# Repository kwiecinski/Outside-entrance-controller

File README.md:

# Outside-entrance-controller
Controller check if someone has entered through the gate/wicket (using photocell) or rang the bell switch. Then sends information by radio module to the receiver that gives a sound signal.

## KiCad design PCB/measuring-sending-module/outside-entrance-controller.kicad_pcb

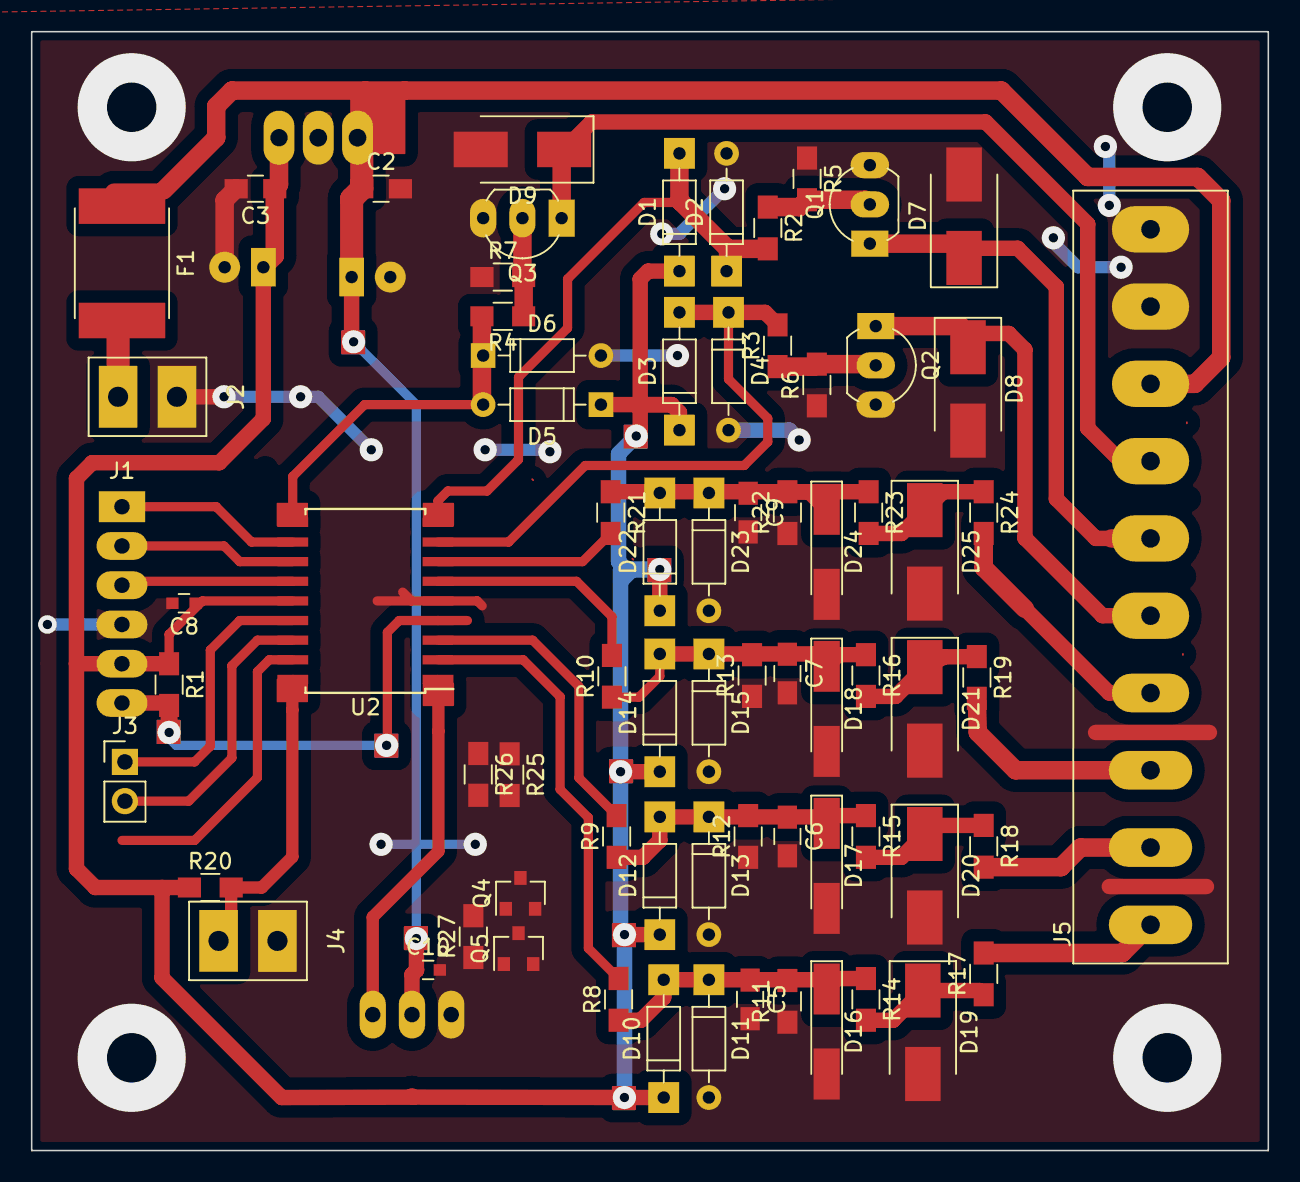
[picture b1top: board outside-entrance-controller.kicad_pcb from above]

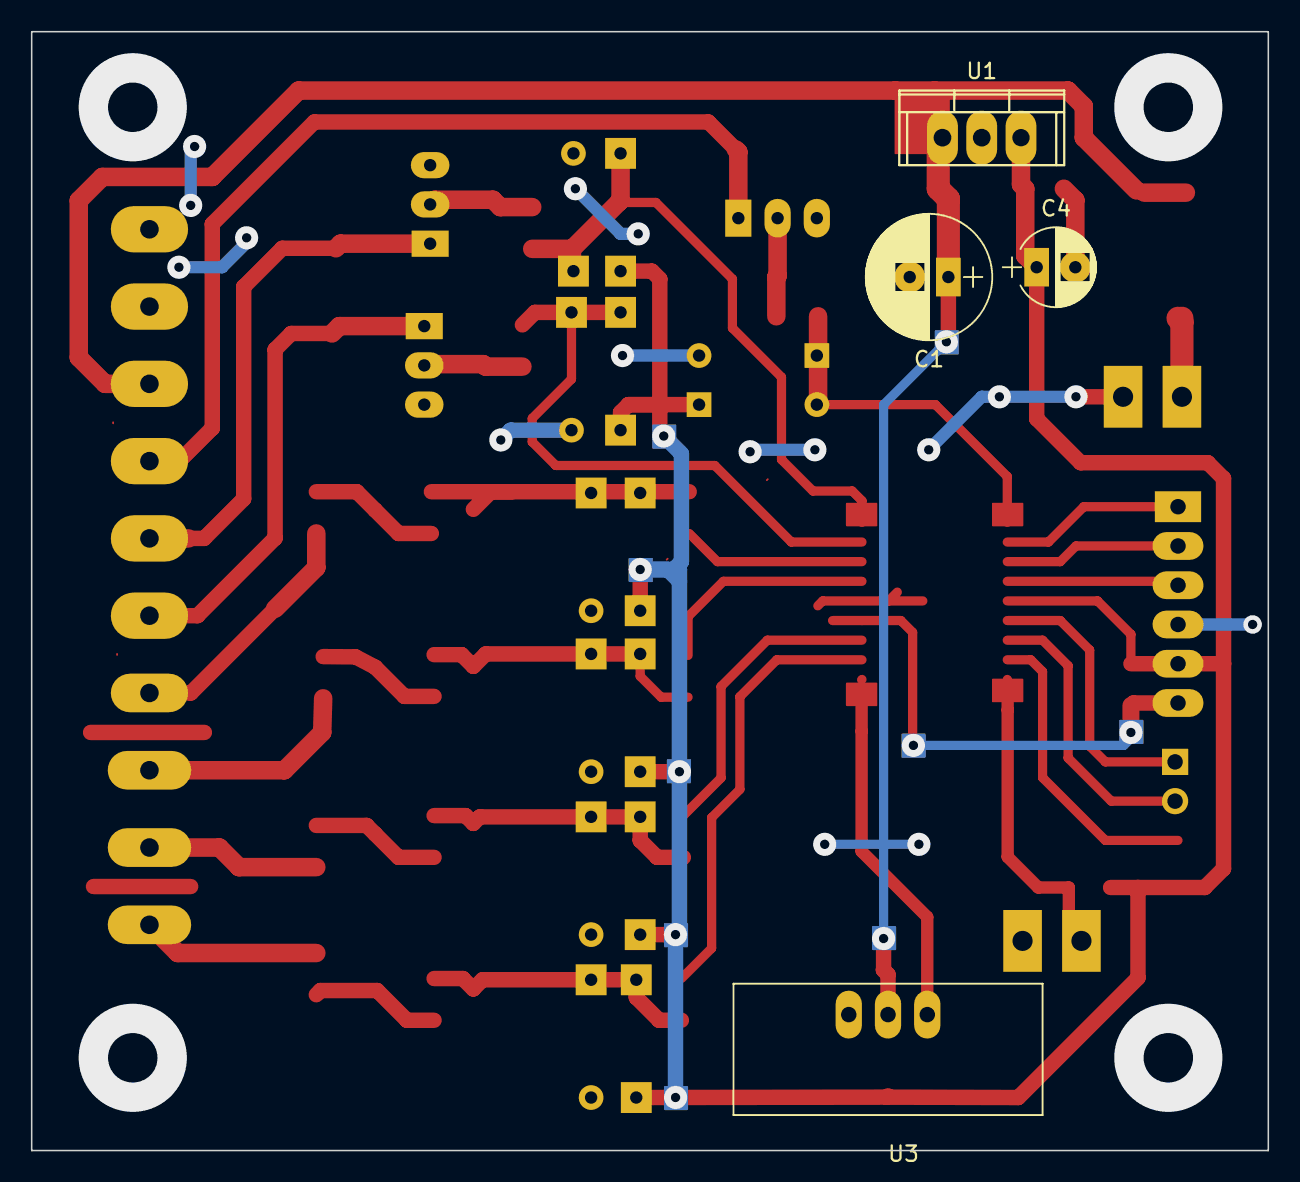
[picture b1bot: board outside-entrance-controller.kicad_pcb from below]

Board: 2 copper layers, 80.0 x 72.4 mm, 76 parts (4 on the bottom side), 42 nets.

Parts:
C1: 470u; CP_Radial_D8.0mm_P2.50mm
C2, C3: 100n; C_0805_HandSoldering
C4: 100u; CP_Radial_D5.0mm_P2.50mm
C5, C6, C7, C9: C; C_0805_HandSoldering
C8, C10: 100n; C_0603
D1, D2, D3, D4, D5, D6, D10, D11, D12, D13, D14, D15, D22, D23: 1N4148; D_DO-35_SOD27_P7.62mm_Horizontal
D7: x; D_SMB_Handsoldering
D8, D9, D19, D20, D21, D25: D_TVS; D_SMB_Handsoldering
D16, D17, D18, D24: 4V7; D_MiniMELF_Handsoldering
F1: 1,5A; Fuse_SMD2920
J1: ICP; Pin_Header_Straight_1x06_Pitch2.54mm
J2: Power-Supply-12V; Conn_1x2_wire
J3: Conn_01x02; Pin_Header_Straight_1x02_Pitch2.54mm
J4: Gate-SW; Conn_1x2_wire
J5: Screw_Terminal_01x10; Screw-Terminal-5.00mm-10pin
Q1, Q2, Q3: BC547; TO-92_Inline_Wide
Q4: BC807; SOT-23
Q5: BC817; SOT-23
R1, R5, R6, R7, R20, R26, R27: 10k; R_0805_HandSoldering
R2, R3, R4: 2k2; R_0805_HandSoldering
R8, R9, R10, R21: 1M; R_0805_HandSoldering
R11, R12, R13, R22: 100k; R_0805_HandSoldering
R14, R15, R16, R23: 1k; R_0805_HandSoldering
R17, R18, R19, R24: 10R; R_0805_HandSoldering
R25: 4k7; R_0805_HandSoldering
U1: L7805; TO-220
U2: PIC16F819-ISO; SOIC-18W_7.5x11.6mm_Pitch1.27mm
U3: 433MHz-Transmitter; 433MHz-Trasmitter

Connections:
+5V: C3.1, C4.1, C8.1, D1.1, D3.1, D5.1, D10.1, D12.1, D14.1, D22.1, J1.5, R1.1, R20.1, U1.3, U2.14
+12V: C1.1, C2.1, C10.1, F1.1, J5.8, Q4.2, R26.2, U1.1
/PGC: J1.2, U2.12
/PGD: J1.3, U2.13
/RA6: J3.1, U2.15
/RA7: J3.2, U2.16
/RST: J1.6, R1.2, U2.4
/TX: J1.1, U2.11
/bell_wicket: J5.3, R19.2
/bell_wicket_uc: R10.2, U2.6
/gate_sw: J4.2, R20.2, U2.18
/input_1: J5.4, R24.2
/input_1_uc: R21.2, U2.7
/open_gate: D7.1, J5.6, Q1.1
/open_gate_uc: D1.2, D2.1, R2.2, U2.9
/output_1: D9.1, J5.7, Q3.1
/output_1_uc: D5.2, D6.1, R4.2, U2.10
/output_2: D8.1, J5.5, Q2.1
/output_2_uc: D3.2, D4.1, R3.2, U2.8
/phs_gate: J5.2, R18.2
/phs_gate_uc: R9.2, U2.3
/phs_wicket: J5.1, R17.2
/phs_wicket_uc: R8.2, U2.2
/radio_en: R27.2, U2.17
/radio_tx: U2.1, U3.1
GND: C1.2, C2.2, C3.2, C4.2, C5.2, C6.2, C7.2, C8.2, C9.2, C10.2, D2.2, D4.2, D6.2, D7.2, D8.2, D9.2, D11.2, D13.2, D15.2, D16.2, D17.2, D18.2, D19.2, D20.2, D21.2, D23.2, D24.2, D25.2, J1.4, J2.1, J4.1, J5.9, J5.10, Q1.3, Q2.3, Q3.3, Q5.2, R5.1, R6.1, R7.1, R11.1, R12.1, R13.1, R22.1, U1.2, U2.5, U3.3
unnamed: C5.1, D10.2, D11.1, D16.1, R8.1, R11.2, R14.1
unnamed: C6.1, D12.2, D13.1, D17.1, R9.1, R12.2, R15.1
unnamed: C7.1, D14.2, D15.1, D18.1, R10.1, R13.2, R16.1
unnamed: C9.1, D22.2, D23.1, D24.1, R21.1, R22.2, R23.1
unnamed: D19.1, R14.2, R17.1
unnamed: D20.1, R15.2, R18.1
unnamed: D21.1, R16.2, R19.1
unnamed: D25.1, R23.2, R24.1
unnamed: F1.2, J2.2
unnamed: Q1.2, R2.1, R5.2
unnamed: Q2.2, R3.1, R6.2
unnamed: Q3.2, R4.1, R7.2
unnamed: Q4.1, R25.2
unnamed: Q4.3, U3.2
unnamed: Q5.1, R27.1
unnamed: Q5.3, R25.1, R26.1

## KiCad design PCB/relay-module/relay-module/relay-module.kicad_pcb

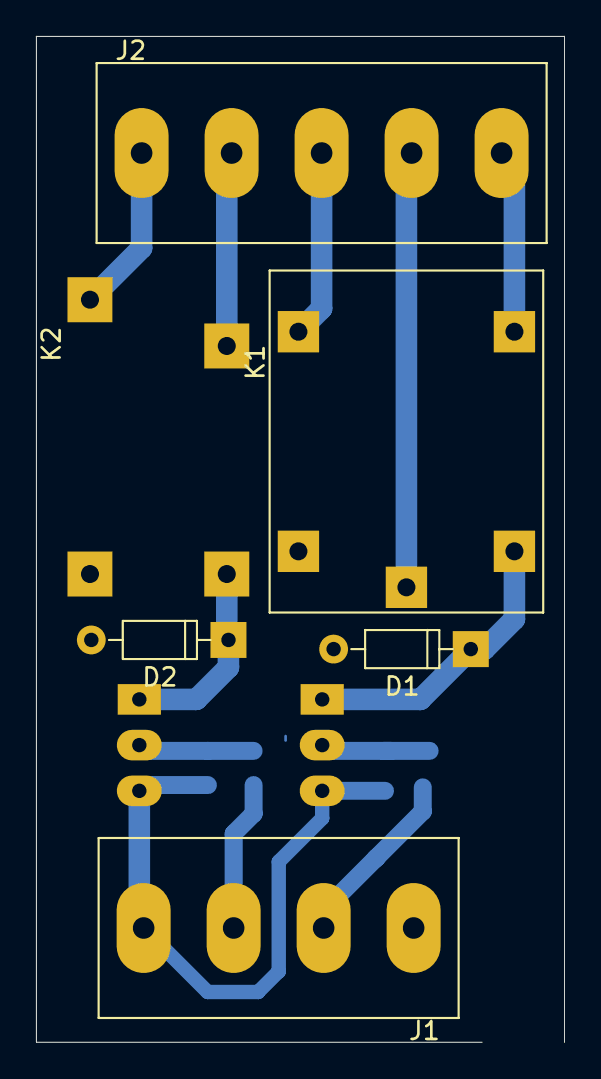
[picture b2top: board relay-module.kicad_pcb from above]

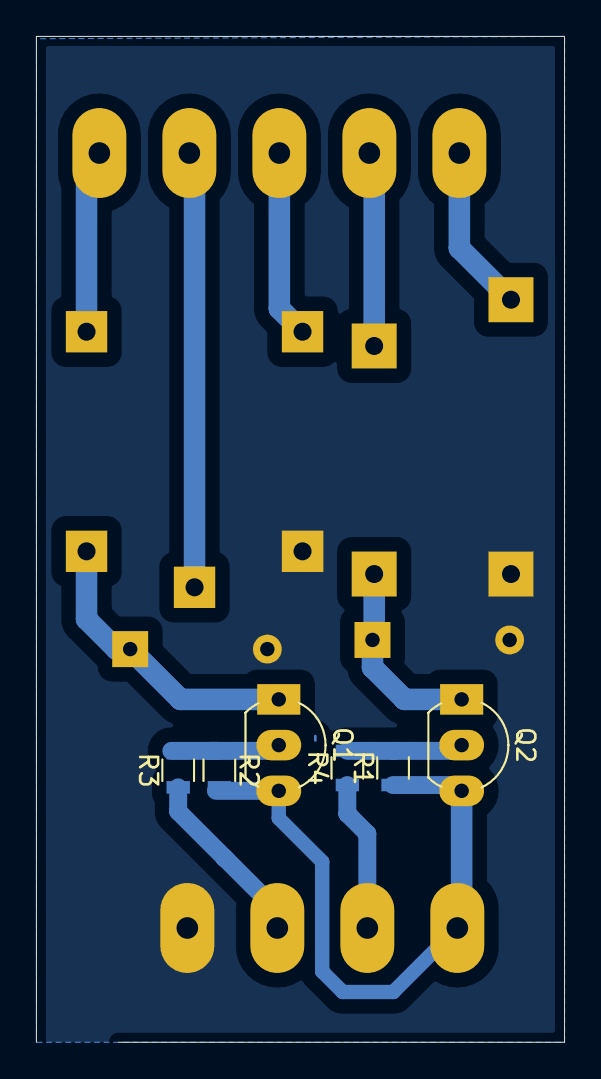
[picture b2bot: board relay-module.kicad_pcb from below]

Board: 2 copper layers, 29.3 x 55.9 mm, 12 parts (6 on the bottom side), 13 nets.

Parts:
D1, D2: 1N4148; D_DO-35_SOD27_P7.62mm_Horizontal
J1: Conn_01x04; Screw-Terminal-5.00mm-4pin
J2: Conn_01x05; Screw-Terminal-5.00mm-5pin
K1: HF3FD-012-ZTF; HF3FD
K2: JZC-40F; JZC-40F_Relay
Q1, Q2: BC557; TO-92_Inline_Wide
R1, R2: 10k; R_0805
R3, R4: 4k7; R_0805

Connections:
+12V: J1.4, Q1.3, Q2.3, R1.1, R2.2
GND: D1.A, D2.A, J1.1, K1.C1, K2.2
unnamed: D1.C, K1.C2, Q1.1
unnamed: D2.C, K2.1, Q2.1
unnamed: J1.2, R3.1
unnamed: J1.3, R4.1
unnamed: J2.1, K2.3
unnamed: J2.2, K2.4
unnamed: J2.3, K1.NO
unnamed: J2.4, K1.COM
unnamed: J2.5, K1.NC
unnamed: Q1.2, R2.1, R3.2
unnamed: Q2.2, R1.2, R4.2

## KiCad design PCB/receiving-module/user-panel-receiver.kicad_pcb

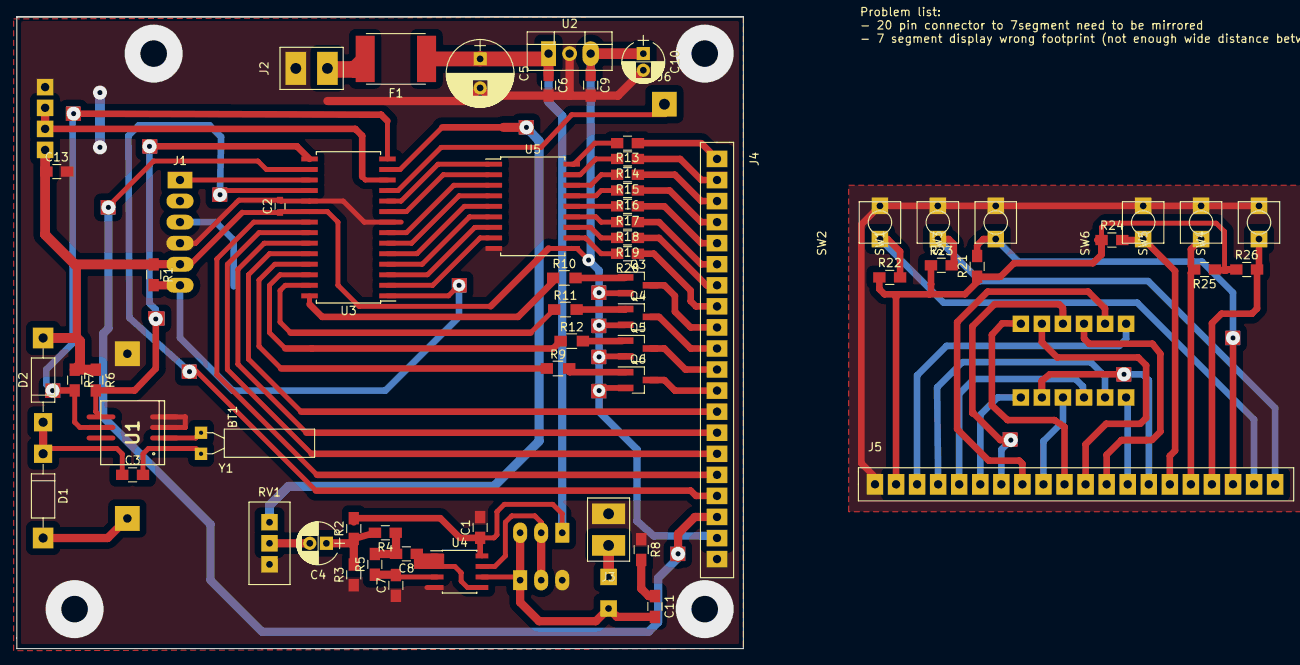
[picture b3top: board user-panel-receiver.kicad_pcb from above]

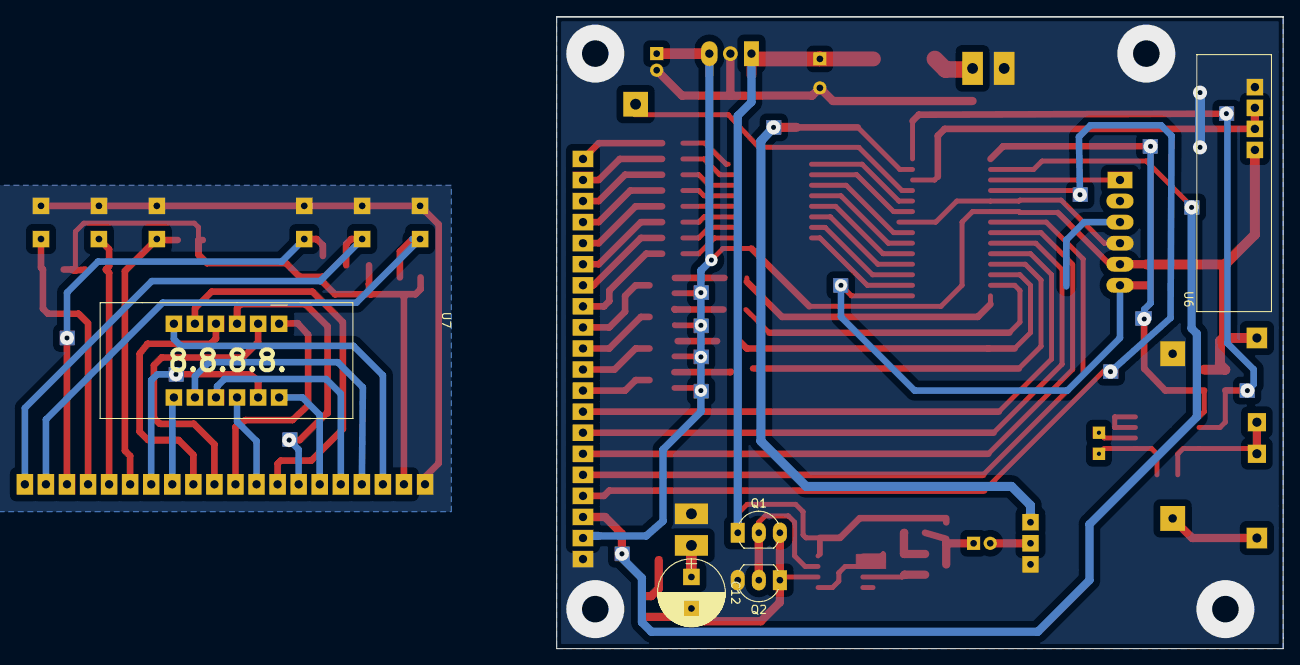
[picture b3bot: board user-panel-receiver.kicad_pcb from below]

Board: 2 copper layers, 87.6 x 76.2 mm, 70 parts (5 on the bottom side), 86 nets.

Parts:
BT1: Battery_Cell; CR2032H
C1, C6, C9, C11, C13: 100n; C_0805_HandSoldering
C2: 100n; C_0603
C3: 22p; C_0805_HandSoldering
C4: 47u; CP_Radial_D5.0mm_P2.00mm
C5: 470u; CP_Radial_D8.0mm_P3.50mm
C7, C8: 10n; C_0805_HandSoldering
C10: 100u; CP_Radial_D5.0mm_P2.00mm
C12: 470u; CP_Radial_D8.0mm_P3.80mm
D1, D2: D_Schottky; D_DO-41_SOD81_P10.16mm_Horizontal
F1: 500m; Fuse_SMD2920
J1: ICP; Pin_Header_Straight_1x06_Pitch2.54mm
J2: Power-Supply; Conn_1x2_wire
J3: Speaker; Conn_1x2_wire
J4, J5: Conn_01x20; Conn-01x20
J6: Conn_01x01; WIRE_PAD_1,3mm
Q1: BC547; TO-92_Inline_Wide
Q2: BC557; TO-92_Inline_Wide
Q3, Q4, Q5, Q6: BC807; SOT-23_Handsoldering
R1, R6, R7, R21, R22, R23, R24, R25, R26: 10k; C_0805_HandSoldering
R2, R3: 2k2; C_0805_HandSoldering
R4, R5: 18k; C_0805_HandSoldering
R8: 10R; C_0805_HandSoldering
R9, R10, R11, R12: 4k7; R_0805_HandSoldering
R13, R14, R15, R16, R17, R18, R19, R20: 330R; C_0805_HandSoldering
RV1: 10k; Potentiometer_Trimmer_Suntan_TSR-3386C_Vertical
SW1: SW_UP; Micro-Switch-5mm-2pin
SW2: SW_DOWN; Micro-Switch-5mm-2pin
SW3: SW_RIGHT; Micro-Switch-5mm-2pin
SW4: SW_SET_RTC; Micro-Switch-5mm-2pin
SW5: SW_TIME1; Micro-Switch-5mm-2pin
SW6: SW_TIME2; Micro-Switch-5mm-2pin
U1: PCF8583; SOT176-1
U2: LM7805; TO-220-3_Vertical
U3: PIC16F886-IP; SOIC-28W_7.5x17.9mm_Pitch1.27mm
U4: LM358; SOIC-8_3.9x4.9mm_Pitch1.27mm
U5: ULN2803A; SOIC-18W_7.5x11.6mm_Pitch1.27mm
U6: FSK100a-Receiver
U7: CA56-12CGKWA; 4-digit-7-segment-display
Y1: Crystal; Crystal_AT310_d3.0mm_l10.0mm_Horizontal

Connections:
+5V: C2.1, C9.1, C10.1, C13.1, D2.2, J1.5, J4.19, Q3.2, Q4.2, Q5.2, Q6.2, R1.1, R6.1, R7.1, U2.3, U3.20, U5.10, U6.1
+5V_1: J5.2, R21.1, R22.1, R23.1, R24.1, R25.1, R26.1
+9V: C1.1, C5.1, C6.1, F1.1, Q1.1, R2.2, U2.1, U4.8
/DIG1: J5.6, U7.12
/DIG1_P: J4.9, Q3.3
/DIG1_Q_PGD: J1.3, R10.1, U3.28
/DIG2: J5.5, U7.9
/DIG2_P: J4.10, Q4.3
/DIG2_Q_PGC: J1.2, R11.1, U3.27
/DIG3: J5.4, U7.8
/DIG3_P: J4.11, Q5.3
/DIG3_Q: R12.1, U3.26
/DIG4: J5.3, U7.6
/DIG4_P: J4.12, Q6.3
/DIG4_Q: R9.1, U3.25
/DISP_A: J5.14, U7.11
/DISP_A_P: J4.1, R13.1
/DISP_B: J5.13, U7.7
/DISP_B_P: J4.2, R14.1
/DISP_C: J5.12, U7.4
/DISP_C_P: J4.3, R15.1
/DISP_D: J5.11, U7.2
/DISP_DP: J5.7, U7.3
/DISP_DP_P: J4.8, R20.1
/DISP_D_P: J4.4, R16.1
/DISP_E: J5.10, U7.1
/DISP_E_P: J4.5, R17.1
/DISP_F: J5.9, U7.10
/DISP_F_P: J4.6, R18.1
/DISP_G: J5.8, U7.5
/DISP_G_P: J4.7, R19.1
/RADIO_RX: U3.12, U6.2
/RST: J1.6, R1.2, U3.1
/RTC_SCI: R7.2, U1.6, U3.14
/RTC_SDA: R6.2, U1.5, U3.15
/SEG_A_uc: U3.10, U5.1
/SEG_B_uc: U3.9, U5.2
/SEG_C_uc: U3.7, U5.3
/SEG_DP_uc: U3.2, U5.8
/SEG_D_uc: U3.6, U5.4
/SEG_E_uc: U3.5, U5.5
/SEG_F_uc: U3.4, U5.6
/SEG_G_uc: U3.3, U5.7
/SPEAKER: RV1.1, U3.13
/SW_DOWN: J5.19, R22.2, SW2.1
/SW_DOWN_uc: J4.14, U3.23
/SW_RIGHT: J5.18, R21.2, SW3.1
/SW_RIGHT_uc: J4.15, U3.22
/SW_SET_RTC: J5.17, R26.2, SW4.1
/SW_SET_RTC_uc: J4.16, U3.21
/SW_TIME1: J5.16, R25.2, SW5.1
/SW_TIME1_uc: J4.17, U3.18
/SW_TIME2: J5.15, R24.2, SW6.1
/SW_TIME2_uc: J4.18, U3.16
/SW_UP: J5.20, R23.2, SW1.1
/SW_UP_uc: J4.13, U3.24
/TX: J1.1, U3.17
GND: BT1.2, C1.2, C2.2, C5.2, C6.2, C7.1, C9.2, C10.2, C13.2, J1.4, J2.1, J3.2, J4.20, Q2.3, R3.1, R8.1, RV1.3, U1.3, U1.4, U2.2, U3.8, U3.19, U4.4, U5.9, U6.3
GNDA: J5.1, SW1.2, SW2.2, SW3.2, SW4.2, SW5.2, SW6.2
unnamed: BT1.1, D1.2
unnamed: C3.1, D1.1, D2.1, U1.8
unnamed: C3.2, U1.1, Y1.1
unnamed: C4.1, R2.1, R3.2, R4.2
unnamed: C4.2, RV1.2
unnamed: C7.2, R5.1, U4.3
unnamed: C8.1, U4.1, U4.2, U4.5
unnamed: C8.2, R4.1, R5.2
unnamed: C11.1, R8.2
unnamed: C11.2, C12.2, Q1.3, Q2.1, U4.6
unnamed: C12.1, J3.1
unnamed: F1.2, J2.2
unnamed: J6.1, U3.11
unnamed: Q1.2, Q2.2, U4.7
unnamed: Q3.1, R10.2
unnamed: Q4.1, R11.2
unnamed: Q5.1, R12.2
unnamed: Q6.1, R9.2
unnamed: R13.2, U5.18
unnamed: R14.2, U5.17
unnamed: R15.2, U5.16
unnamed: R16.2, U5.15
unnamed: R17.2, U5.14
unnamed: R18.2, U5.13
unnamed: R19.2, U5.12
unnamed: R20.2, U5.11
unnamed: U1.2, Y1.2

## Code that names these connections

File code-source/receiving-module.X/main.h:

#ifndef DEFINE_H
#define	DEFINE_H

#define _XTAL_FREQ 8000000

#pragma config FOSC = INTRC_NOCLKOUT// Oscillator Selection bits (INTOSCIO oscillator: I/O function on RA6/OSC2/CLKOUT pin, I/O function on RA7/OSC1/CLKIN)
#pragma config WDTE = OFF       // Watchdog Timer Enable bit (WDT disabled and can be enabled by SWDTEN bit of the WDTCON register)
#pragma config PWRTE = OFF      // Power-up Timer Enable bit (PWRT disabled)
#pragma config MCLRE = ON       // RE3/MCLR pin function select bit (RE3/MCLR pin function is MCLR)
#pragma config CP = OFF         // Code Protection bit (Program memory code protection is disabled)
#pragma config CPD = OFF        // Data Code Protection bit (Data memory code protection is disabled)
#pragma config BOREN = OFF      // Brown Out Reset Selection bits (BOR disabled)
#pragma config IESO = OFF       // Internal External Switchover bit (Internal/External Switchover mode is disabled)
#pragma config FCMEN = OFF      // Fail-Safe Clock Monitor Enabled bit (Fail-Safe Clock Monitor is disabled)
#pragma config LVP = OFF        // Low Voltage Programming Enable bit (RB3 pin has digital I/O, HV on MCLR must be used for programming)

// CONFIG2
#pragma config BOR4V = BOR40V   // Brown-out Reset Selection bit (Brown-out Reset set to 4.0V)
#pragma config WRT = OFF        // Flash Program Memory Self Write Enable bits (Write protection off)

typedef struct 
{
	unsigned char frame[4];
    unsigned char RCV_Frame;
    
}DataStruct;


typedef struct 
{
	unsigned char seconds,minutes,hours,day,month,year;	
	
}TimeStruct;

typedef struct
{
    unsigned char klock, pin, lock_long_press;
    volatile unsigned char *port;
    void (*button_short_function)(void); 
    void (*button_long_function)(void);
 
}KeyStruct;

typedef struct
{
    KeyStruct *set_rtc;
    KeyStruct *set_time1;
    KeyStruct *set_time2;
    KeyStruct *set_right;
    KeyStruct *set_up;
    KeyStruct *set_down;
    
}KeyPointerStruct;

/*
#define SW_TIME1    PORTCbits.RC7
#define SW_TIME2    PORTCbits.RC5
#define SW_SET_RTC  PORTBbits.RB0
#define SW_RIGHT    PORTBbits.RB1
#define SW_DOWN     PORTBbits.RB2
#define SW_UP       PORTBbits.RB3

*/
#define SW_TIME1_PIN       7
#define SW_TIME1_PORT      PORTC

#define SW_TIME2_PIN       5
#define SW_TIME2_PORT      PORTC

#define SW_SET_RTC_PIN     0
#define SW_SET_RTC_PORT    PORTB

#define SW_RIGHT_PIN       1
#define SW_RIGHT_PORT      PORTB

#define SW_DOWN_PIN        2
#define SW_DOWN_PORT       PORTB

#define SW_UP_PIN          3
#define SW_UP_PORT         PORTB


#endif	/* DEFINE_H */

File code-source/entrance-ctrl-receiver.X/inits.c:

#include <xc.h>


void Global_Init(void)
{
    //Ocillator Config - 8MHz Internal
    OSCCONbits.IRCF=0b111;
    OSCCONbits.OSTS=0;
    OSCCONbits.SCS=1;
    
    //PORTA pins as digital I/O;
    ANSEL=0x00;     
    ANSELH=0x00;
    
    TRISC0=0;    //unconeccted output
    TRISC1=1;    //radio rx
    TRISC2=0;    //speaker
    TRISC3=1;    //rtc sci
    TRISC4=1;    //rtc sda
    TRISC5=1;    //sw time2
    TRISC6=0;    //uart tx
    TRISC7=1;    //sw time1
        
    TRISA0=0;    //seg dp
    TRISA1=0;    //seg g
    TRISA2=0;    //seg f
    TRISA3=0;    //seg e
    TRISA4=0;    //seg d
    TRISA5=0;    //seg c
    TRISA6=0;    //seg a
    TRISA7=0;    //seg b
    
    TRISB0=1;    //sw set rtc
    TRISB1=1;    //sw right
    TRISB2=1;    //sw down
    TRISB3=1;    //sw up
    TRISB4=0;    //dig4 ca
    TRISB5=0;    //dig3 ca
    TRISB6=0;    //dig2 ca
    TRISB7=0;    //dig1 ca 
}

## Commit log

2020-03-01 add control and measuring module PCB
2020-04-28 Receiver and transmiter code update, PCB and schematic update
2020-06-21 Receiver code cleanup
2020-08-20 Receiver lite version
2020-08-30 Add watchdog to transmiter, remove days from receiver and communication fix
2020-09-01 library update
2026-02-20 Revert "UPDATE"
    This reverts commit 271b9db3e12c53c1c8dba2d02026c13778404b14.
